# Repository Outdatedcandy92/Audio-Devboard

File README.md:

# VS1053B Audio Devboard

A compact development board based around the VS1053B audio codec paired with a STM32 microcontroller. The board features a MicroSD card slot, Stereo audio output, Line in, and a bunch of broken GPIO.

---

## Schematics

Schematics pdf is available under the `/PCB` folder and the project's KiCad files can be found under `/PCB/kicad`.

---

## PCB

---

## License

This project is licensed under the CERN Open Hardware Licence Version 2 Weakly Reciprocal [(CERN OHL W)](LICENSE.txt).

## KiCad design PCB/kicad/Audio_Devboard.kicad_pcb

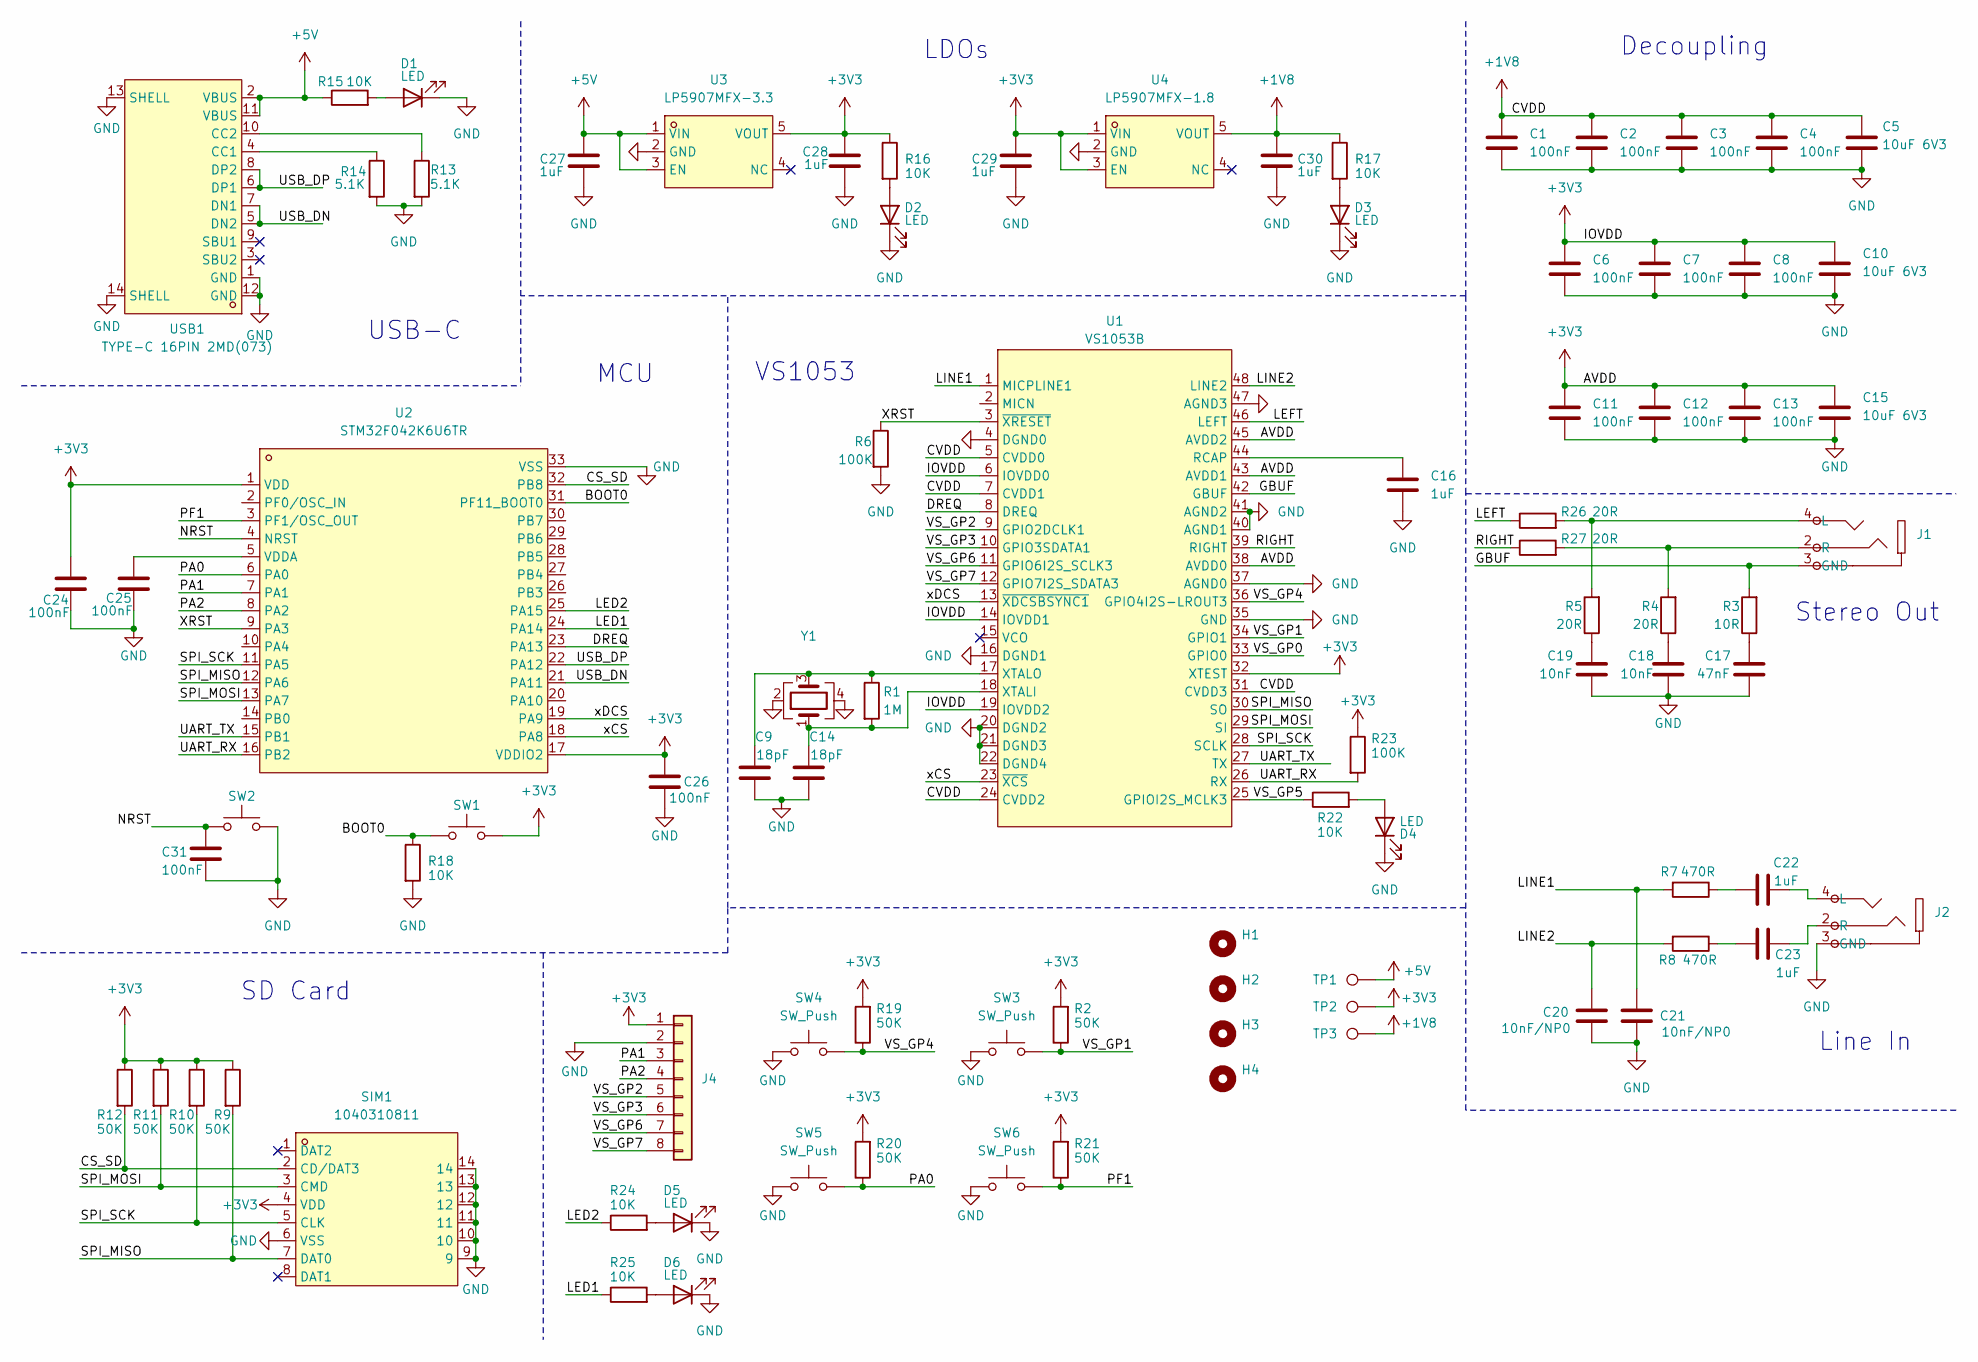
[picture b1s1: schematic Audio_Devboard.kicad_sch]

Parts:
C1, C2, C3, C4, C6, C7, C8, C11, C12, C13, C24, C25, C26, C31: 100nF; C_0402_1005Metric; LCSC Part C1525
C5, C10, C15: 10uF 6V3; C_0402_1005Metric; LCSC Part C315248
C9, C14: 18pF; C_0402_1005Metric; LCSC Part C106202
C16, C22, C23, C27, C28, C29, C30: 1uF; C_0402_1005Metric; LCSC Part C14445
C17: 47nF; C_0402_1005Metric; LCSC Part C368599
C18, C19: 10nF; C_0402_1005Metric; LCSC Part C15195
C20, C21: 10nF/NP0; C_0402_1005Metric; LCSC Part C3855387
D1, D2, D3, D4, D5, D6: LED; LED_0402_1005Metric; LCSC Part C364553
H1, H2, H3, H4: MountingHole; MountingHole_2.7mm_M2.5_ISO7380_Pad_TopBottom
J1, J2: Black headphone jack; AUDIO-TH_PJ-3200; LCSC Part C18166
J4: Conn_01x08; PinHeader_1x08_P2.54mm_Vertical; LCSC Part C6332201
R1: 1M; R_0402_1005Metric; LCSC Part C138033
R2, R9, R10, R11, R12, R19, R20, R21: 50K; R_0402_1005Metric; LCSC Part C166559
R3: 10R; R_0402_1005Metric; LCSC Part C25077
R4, R5, R26, R27: 20R; R_0402_1005Metric; LCSC Part C25089
R6, R23: 100K; R_0402_1005Metric; LCSC Part C25741
R7, R8: 470R; R_0402_1005Metric; LCSC Part C25117
R13, R14: 5.1K; R_0402_1005Metric; LCSC Part C25905
R15, R16, R17, R18, R22, R24, R25: 10K; R_0402_1005Metric; LCSC Part 0402WGF1002TCE C25744 Hot
SIM1: 1040310811; SIM-SMD_8P-1040310811; LCSC Part C585350
SW1, SW2: SW_Push; SW-SMD_L3.9-W3.0-P4.45; LCSC Part C393938
SW3, SW4, SW5, SW6: SW_Push; SW_PUSH_6mm; LCSC Part C393938
TP1, TP2, TP3: TestPoint; TestPoint_Pad_D2.5mm
U1: VS1053B; LQFP-48_L7.0-W7.0-P0.50-LS9.0-BL; LCSC Part C9922
U2: STM32F042K6U6TR; UFQFPN-32_L5.0-W5.0-P0.50-TL-EP3.5; LCSC Part C2053439
U3: LP5907MFX-3.3; SOT-23-5_L3.0-W1.7-P0.95-LS2.8-BR; LCSC Part C23380874
U4: LP5907MFX-1.8; SOT-23-5_L3.0-W1.7-P0.95-LS2.8-BR; LCSC Part C23380872
USB1: TYPE-C 16PIN 2MD(073); USB-C-SMD_TYPE-C-6PIN-2MD-073; LCSC Part C2765186
Y1: SX2B12.288F1210F30; Crystal_SMD_2520-4Pin_2.5x2.0mm; LCSC Part C49253544

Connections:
+1V8: C1.1, C2.1, C3.1, C4.1, C5.1, C30.1, R17.1, TP3.1, U1.5 (CVDD0), U1.7 (CVDD1), U1.24 (CVDD2), U1.31 (CVDD3), U4.5 (VOUT)
+3V3: C6.1, C7.1, C8.1, C10.1, C11.1, C12.1, C13.1, C15.1, C24.1, C26.1, C28.1, C29.1, J4.1, R2.2, R9.1, R10.1, R11.1, R12.1, R16.1, R19.2, R20.2, R21.2, R23.1, SIM1.4 (VDD), SW1.2, TP2.1, U1.6 (IOVDD0), U1.14 (IOVDD1), U1.19 (IOVDD2), U1.32 (XTEST), U1.38 (AVDD0), U1.43 (AVDD1), U1.45 (AVDD2), U2.1 (VDD), U2.17 (VDDIO2), U3.5 (VOUT), U4.1 (VIN), U4.3 (EN)
+5V: C27.1, R15.1, TP1.1, U3.1 (VIN), U3.3 (EN), USB1.2 (VBUS), USB1.11 (VBUS)
/BOOT0: R18.1, SW1.1, U2.31 (PF11_BOOT0)
/CS_SD: R12.2, SIM1.2 (CD/DAT3), U2.32 (PB8)
/DREQ: U1.8 (DREQ), U2.23 (PA13)
/GBUF: J1.3 (GND), R3.2, U1.42 (GBUF)
/LED1: R25.1, U2.24 (PA14)
/LED2: R24.1, U2.25 (PA15)
/LEFT: R26.1, U1.46 (LEFT)
/LINE1: C21.2, R7.2, U1.1 (MICPLINE1)
/LINE2: C20.2, R8.2, U1.48 (LINE2)
/NRST: C31.2, SW2.1, U2.4 (NRST)
/PA0: R20.1, SW5.2, U2.6 (PA0)
/PA1: J4.3, U2.7 (PA1)
/PA2: J4.4, U2.8 (PA2)
/PF1: R21.1, SW6.2, U2.3 (PF1/OSC_OUT)
/RIGHT: R27.1, U1.39 (RIGHT)
/SPI_MISO: R9.2, SIM1.7 (DAT0), U1.30 (SO), U2.12 (PA6)
/SPI_MOSI: R11.2, SIM1.3 (CMD), U1.29 (SI), U2.13 (PA7)
/SPI_SCK: R10.2, SIM1.5 (CLK), U1.28 (SCLK), U2.11 (PA5)
/UART_RX: R23.2, U1.26 (RX), U2.16 (PB2)
/UART_TX: U1.27 (TX), U2.15 (PB1)
/USB_DN: U2.21 (PA11), USB1.5 (DN2), USB1.7 (DN1)
/USB_DP: U2.22 (PA12), USB1.6 (DP1), USB1.8 (DP2)
/VS_GP0: U1.33 (GPIO0)
/VS_GP1: R2.1, SW3.2, U1.34 (GPIO1)
/VS_GP2: J4.5, U1.9 (GPIO2DCLK1)
/VS_GP3: J4.6, U1.10 (GPIO3SDATA1)
/VS_GP4: R19.1, SW4.2, U1.36 (GPIO4I2S-LROUT3)
/VS_GP5: R22.1, U1.25 (GPIOI2S_MCLK3)
/VS_GP6: J4.7, U1.11 (GPIO6I2S_SCLK3)
/VS_GP7: J4.8, U1.12 (GPIO7I2S_SDATA3)
/XRST: R6.1, U1.3 (~XRESET), U2.9 (PA3)
/xCS: U1.23 (~XCS), U2.18 (PA8)
/xDCS: U1.13 (~XDCSBSYNC1), U2.19 (PA9)
GND: C1.2, C2.2, C3.2, C4.2, C5.2, C6.2, C7.2, C8.2, C9.1, C10.2, C11.2, C12.2, C13.2, C14.1, C15.2, C16.2, C17.2, C18.2, C19.2, C20.1, C21.1, C24.2, C25.2, C26.2, C27.2, C28.2, C29.2, C30.2, C31.1, D1.1 (K), D2.1 (K), D3.1 (K), D4.1 (K), D5.1 (K), D6.1 (K), J2.3 (GND), J4.2, R6.2, R13.2, R14.2, R18.2, SIM1.6 (VSS), SIM1.9, SIM1.10, SIM1.11, SIM1.12, SIM1.13, SIM1.14, SW2.2, SW3.1, SW4.1, SW5.1, SW6.1, U1.4 (DGND0), U1.16 (DGND1), U1.20 (DGND2), U1.21 (DGND3), U1.22 (DGND4), U1.35 (GND), U1.37 (AGND0), U1.40 (AGND1), U1.41 (AGND2), U1.47 (AGND3), U2.33 (VSS), U3.2 (GND), U4.2 (GND), USB1.1 (GND), USB1.12 (GND), USB1.13 (SHELL), USB1.14 (SHELL), Y1.2, Y1.4
unnamed: C17.1, R3.1
unnamed: C18.1, R4.1
unnamed: C19.1, R5.1
unnamed: C22.1, R7.1
unnamed: C23.1, R8.1
unnamed: D1.2 (A), R15.2
unnamed: D2.2 (A), R16.2
unnamed: D3.2 (A), R17.2
unnamed: D4.2 (A), R22.2
unnamed: D5.2 (A), R24.2
unnamed: D6.2 (A), R25.2
unnamed: J1.4 (L), R5.2, R26.2
unnamed: J1.2 (R), R4.2, R27.2
unnamed: C22.2, J2.4 (L)
unnamed: C23.2, J2.2 (R)
unnamed: C16.1, U1.44 (RCAP)
unnamed: C14.2, R1.2, U1.18 (XTALI), Y1.1
unnamed: C9.2, R1.1, U1.17 (XTALO), Y1.3
unnamed: C25.1, U2.5 (VDDA)
unnamed: R14.1, USB1.4 (CC1)
unnamed: R13.1, USB1.10 (CC2)

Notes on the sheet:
Stereo Out
LDOs
Decoupling
MCU
Line In
SD Card
VS1053
USB-C

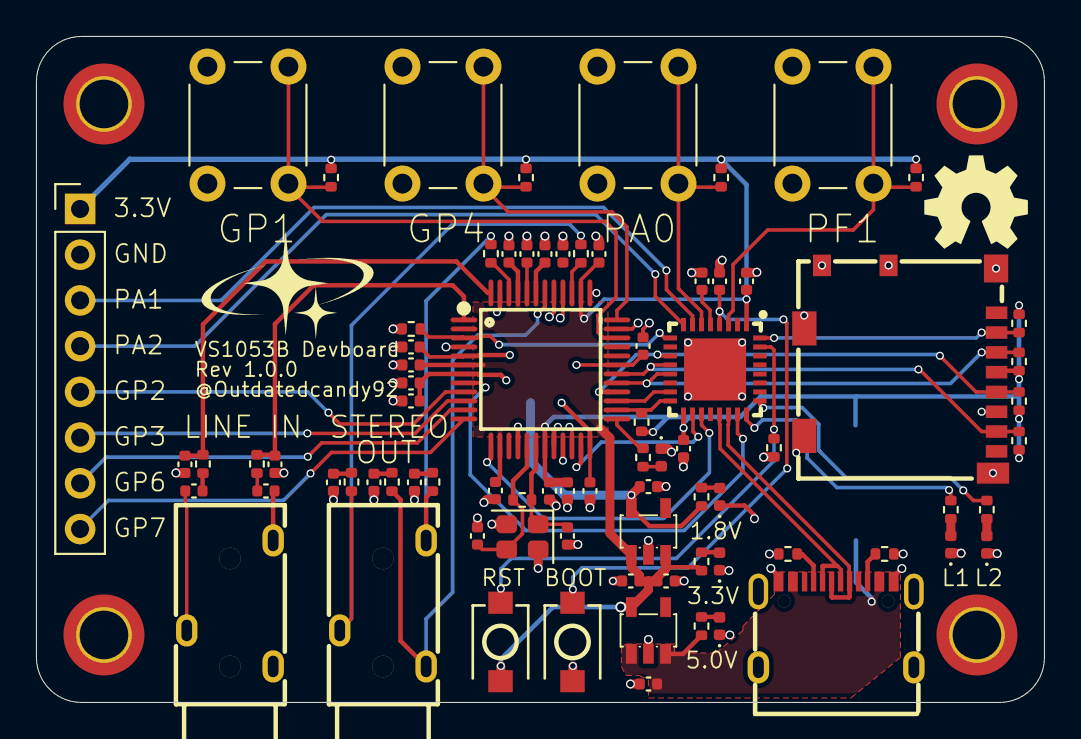
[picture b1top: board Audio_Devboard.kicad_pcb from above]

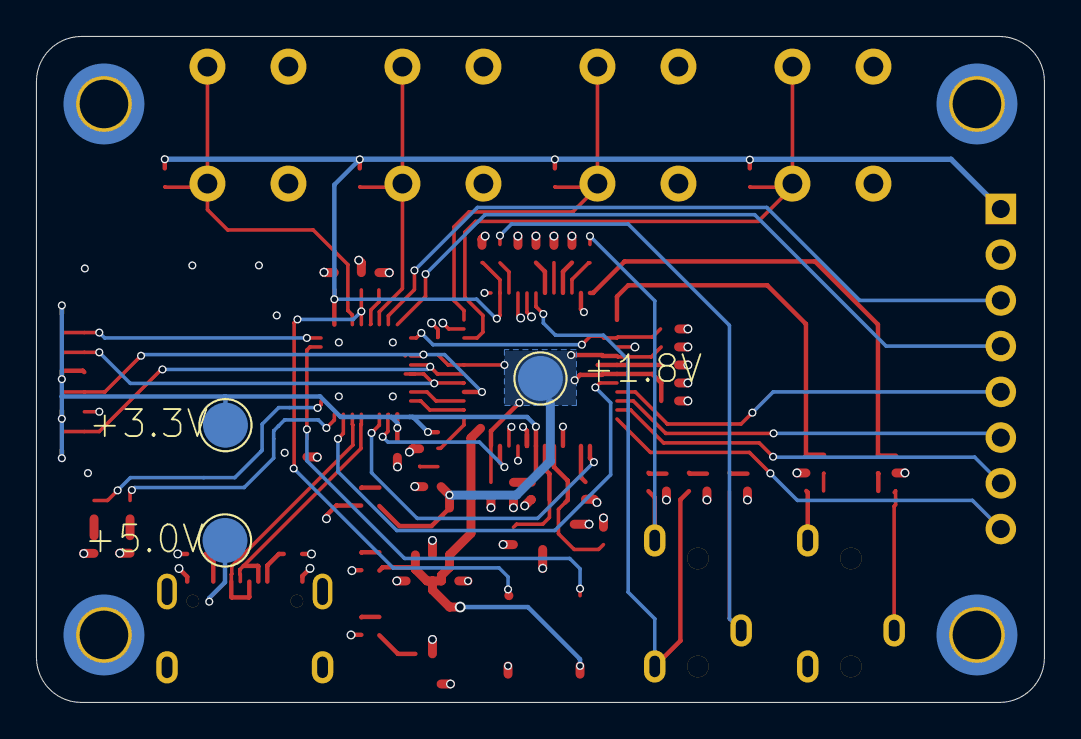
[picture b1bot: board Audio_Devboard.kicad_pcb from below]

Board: 4 copper layers, 56.0 x 37.0 mm, 87 parts (3 on the bottom side), 57 nets.

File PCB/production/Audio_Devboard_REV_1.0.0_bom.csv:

Designator,Footprint,Quantity,Value,LCSC Part #
"C1, C11, C12, C13, C2, C24, C25, C26, C3, C31, C4, C6, C7, C8",0402,14,100nF,C1525
"C10, C15, C5",0402,3,10uF 6V3,C315248
"C14, C9",0402,2,18pF,C106202
"C16, C22, C23, C27, C28, C29, C30",0402,7,1uF,C14445
C17,0402,1,47nF,C368599
"C18, C19",0402,2,10nF,C15195
"C20, C21",0402,2,10nF/NP0,C3855387
"D1, D2, D3, D4, D5, D6",0402,6,LED,C364553
"J1, J2",AUDIO-TH_PJ-3200,2,Black headphone jack,C18166
J4,PinHeader_1x08_P2.54mm_Vertical,1,Conn_01x08,C6332201
R1,0402,1,1M,C138033
"R10, R11, R12, R19, R2, R20, R21, R9",0402,8,50K,C166559
"R13, R14",0402,2,5.1K,C25905
"R15, R16, R17, R18, R22, R24, R25",0402,7,10K, 0402WGF1002TCE C25744 Hot 
"R23, R6",0402,2,100K,C25741
"R26, R27, R4, R5",0402,4,20R,C25089
R3,0402,1,10R,C25077
"R7, R8",0402,2,470R,C25117
SIM1,SIM-SMD_8P-1040310811,1,1040310811,C585350
"SW1, SW2",SW-SMD_L3.9-W3.0-P4.45,2,SW_Push,C393938
"SW3, SW4, SW5, SW6",SW_PUSH_6mm,4,SW_Push,C393938
U1,LQFP-48_L7.0-W7.0-P0.50-LS9.0-BL,1,VS1053B,C9922
U2,UFQFPN-32_L5.0-W5.0-P0.50-TL-EP3.5,1,STM32F042K6U6TR,C2053439
U3,SOT-23-5_L3.0-W1.7-P0.95-LS2.8-BR,1,LP5907MFX-3.3,C23380874
U4,SOT-23-5_L3.0-W1.7-P0.95-LS2.8-BR,1,LP5907MFX-1.8,C23380872
USB1,USB-C-SMD_TYPE-C-6PIN-2MD-073,1,TYPE-C 16PIN 2MD(073),C2765186
Y1,Crystal_SMD_2520-4Pin_2.5x2.0mm,1,SX2B12.288F1210F30,C49253544

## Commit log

2025-12-24 added pcb
2025-12-24 Rev 1.0.0
2025-12-24 journal update
